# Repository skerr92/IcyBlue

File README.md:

# IcyBlue Feather FPGA Development Board

<image src="https://github.com/skerr92/IcyBlue/blob/main/Images/IMG_0353.jpg">

Welcome to the home of the IcyBlue Feather, an FPGA based development board designed to be integrated into the Adafruit Feather ecosystem of Feathers and Feather Wings.

The goal of this repository is to be the single source of truth for the IcyBlue Feather. Containing all the relevant articles including images, schematics, usage examples, board files, and other important documentation.

Questions? Email [hello@oakdev.tech](mailto:hello@oakdev.tech)

### Documentation ###

All documentation can be found under the [Documentation](https://github.com/skerr92/IcyBlue/tree/main/Documentation) directory of this repository. This will include data sheets, usage guides, application notes, errata, and other important documents.

Documentation quick links:
* Data sheet: [IcyBlue Overview Data Sheet](https://github.com/skerr92/IcyBlue/blob/main/Documentation/IcyBlue%20Feather%20Datasheet%20rev1a.pdf)
* Board files: [EagleCAD Board Files](https://github.com/skerr92/IcyBlue/blob/main/Documentation/Lattice%20FPGA%20standard%20feather%20wing.brd)
* Schematic files: [EagleCAD Schematic Files](https://github.com/skerr92/IcyBlue/blob/main/Documentation/Lattice%20FPGA%20standard%20feather%20wing.sch)

### Schematic ###

Represented below is the Rev 1a schematic. This is the current production schematic for the IcyBlue Feather. If major hardware changes are added, additional labeled schematic images can be found here and in the [documentation directory](https://github.com/skerr92/IcyBlue/tree/main/Documentation).

<image src="https://github.com/skerr92/IcyBlue/blob/main/Images/IcyBlue%20Feather%20Schematic.png">

### Usage Examples ###

All usage examples including the RGB sequence example that ships with the board can be found in the [examples repository](https://github.com/skerr92/ice5lp4k_examples).

Examples Quick Links:
* [RGB Blink](https://github.com/skerr92/ice5lp4k_examples/tree/master/leds)
* [DSP Example](https://github.com/skerr92/ice5lp4k_examples/tree/master/dsp)

### Errata ###

Any Errate for the IcyBlue Feather will be linked below with the specific dates and errata version.

### Additional Information ###

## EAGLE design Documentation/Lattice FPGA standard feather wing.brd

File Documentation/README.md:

# Directory containing relevant documentation

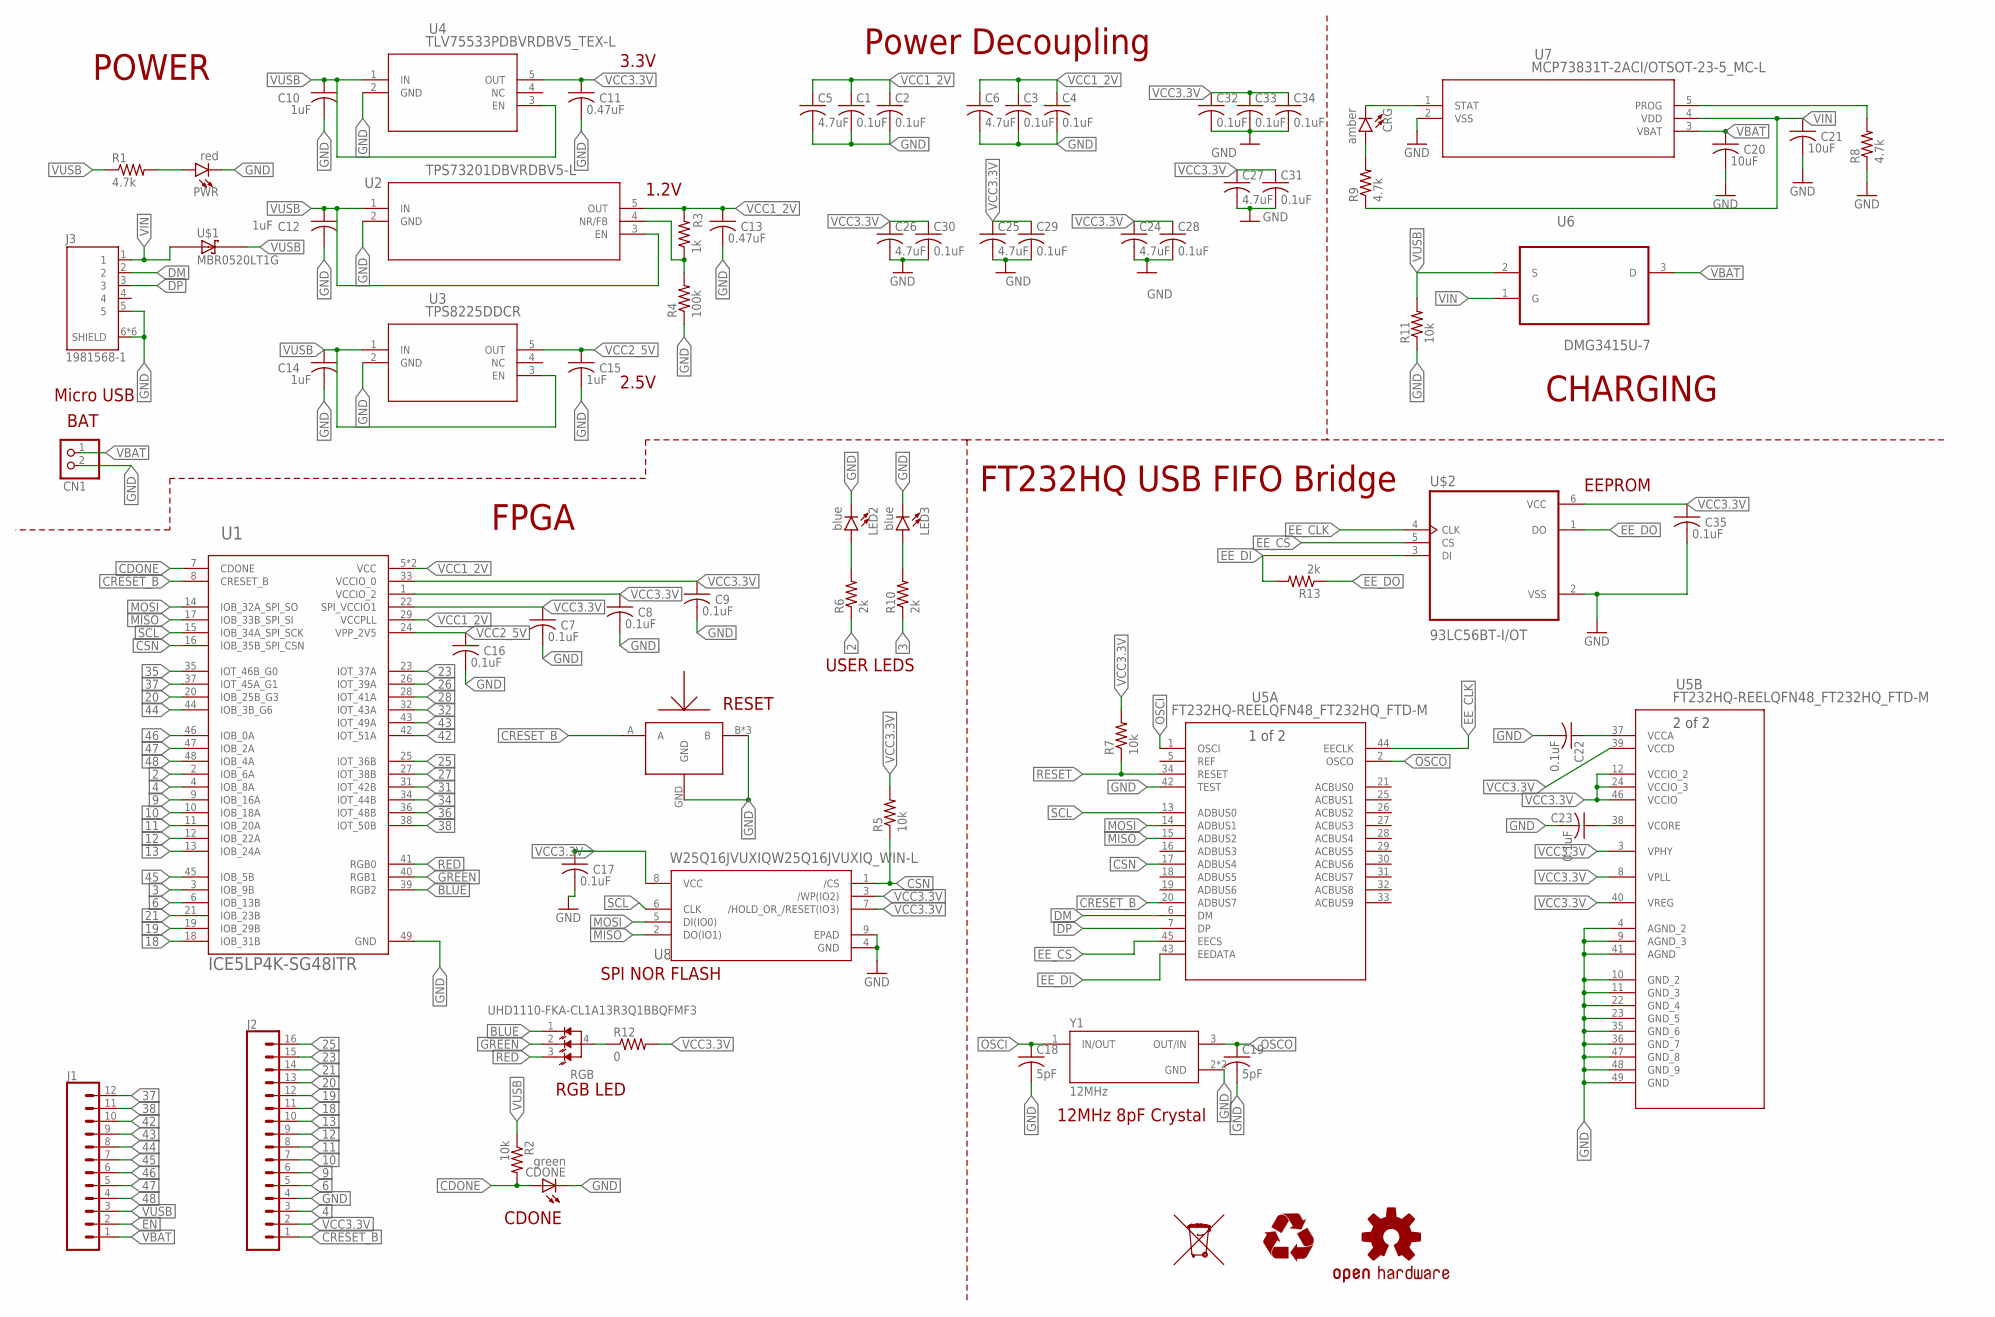
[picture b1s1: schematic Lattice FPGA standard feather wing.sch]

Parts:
C1, C2, C3, C4, C7, C8, C9, C16, C17, C22, C23, C28, C29, C30, C31, C32, C33, C34, C35: 0.1uF; C0402
C5, C6, C24, C25, C26, C27: 4.7uF; C0603
C10, C12, C14, C15: 1uF; C0402
C11, C13: 0.47uF; C0402
C18, C19: 5pF; C0402
C20, C21: 10uF; C0603
CDONE: green; CHIP-LED0603
CN1: JST_2PIN-SMT-RA; JST-PH-2-SMT-RA
CRG: amber; LED-0603
J1: CONN_12NO_SILK; 1X12_NO_SILK
J2: CONN_161X16_NO_SILK; 1X16_NO_SILK
J3: 1981568-1; TE_1981568-1
LED2, LED3: blue; LED-0603
LOGO1: OSHW-LOGOS; OSHW-LOGO-S
PWR: red; LED-0603
R1, R8, R9: 4.7k; R0603
R2, R5, R11: 10k; R0402
R3: 1k; R0402
R4: 100k; R0402
R6, R10, R13: 2k; R0402
R7: 10k; R0603
R12: 0; R0603
RGB: UHD1110-FKA-CL1A13R3Q1BBQFMF3; LED_UHD1110-FKA-CL1A13R3Q1BBQFMF3
U1: ICE5LP4K-SG48ITR; QFN50P700X700X100-49N
U2: TPS73201DBVRDBV5-L; DBV5-L
U3: TPS8225DDCR; DBV5_TEX-L
U4: TLV75533PDBVRDBV5_TEX-L; DBV5_TEX-L
U5: FT232HQ-REELQFN48_FT232HQ_FTD-M; QFN48_FT232HQ_FTD-M
U6: DMG3415U-7; SOT95P240X105-3N
U7: MCP73831T-2ACI/OTSOT-23-5_MC-L; SOT-23-5_MC-L
U8: W25Q16JVUXIQW25Q16JVUXIQ_WIN-L; W25Q16JVUXIQ_WIN-L
U$1: MBR0520LT1G; SOD3716X117(SOD-123)
U$2: 93LC56BT-I/OT; SOT95P280X145-6N
U$3: SOF-232HST; 3.3X2.9
Y1: 12MHz; XTAL_ECS-480-10-37-JTN-TR

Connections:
2: R6.1, U1.2 (IOB_6A)
3: R10.1, U1.3 (IOB_9B)
4: J2.3, U1.4 (IOB_8A)
6: J2.5, U1.6 (IOB_13B)
9: J2.6, U1.9 (IOB_16A)
10: J2.7, U1.10 (IOB_18A)
11: J2.8, U1.11 (IOB_20A)
12: J2.9, U1.12 (IOB_22A)
13: J2.10, U1.13 (IOB_24A)
18: J2.11, U1.18 (IOB_31B)
19: J2.12, U1.19 (IOB_29B)
20: J2.13, U1.20 (IOB_25B_G3)
21: J2.14, U1.21 (IOB_23B)
23: J2.15, U1.23 (IOT_37A)
25: J2.16, U1.25 (IOT_36B)
26: U1.26 (IOT_39A)
27: U1.27 (IOT_38B)
28: U1.28 (IOT_41A)
31: U1.31 (IOT_42B)
32: U1.32 (IOT_43A)
34: U1.34 (IOT_44B)
35: U1.35 (IOT_46B_G0)
36: U1.36 (IOT_48B)
37: J1.12, U1.37 (IOT_45A_G1)
38: J1.11, U1.38 (IOT_50B)
42: J1.10, U1.42 (IOT_51A)
43: J1.9, U1.43 (IOT_49A)
44: J1.8, U1.44 (IOB_3B_G6)
45: J1.7, U1.45 (IOB_5B)
46: J1.6, U1.46 (IOB_0A)
47: J1.5, U1.47 (IOB_2A)
48: J1.4, U1.48 (IOB_4A)
BLUE: RGB.1 (BLUE), U1.39 (RGB2)
CDONE: CDONE.A, R2.2, U1.7 (CDONE)
CRESET_B: J2.1, U1.8 (CRESET_B), U5.20 (ADBUS7), U$3.A
CSN: R5.1, U1.16 (IOB_35B_SPI_CSN), U5.17 (ADBUS4), U8.1 (/CS)
DM: J3.2, U5.6 (DM)
DP: J3.3, U5.7 (DP)
EE_CLK: U5.44 (EECLK), U$2.4 (CLK)
EE_CS: U5.45 (EECS), U$2.5 (CS)
EE_DI: R13.2, U5.43 (EEDATA), U$2.3 (DI)
EE_DO: R13.1, U$2.1 (DO)
EN: J1.2
GND: C1.2, C2.2, C3.2, C4.2, C5.2, C6.2, C7.2, C8.2, C9.2, C10.2, C11.2, C12.2, C13.2, C14.2, C15.2, C16.2, C17.2, C18.2, C19.2, C20.2, C21.2, C22.2, C23.2, C24.2, C25.2, C26.2, C27.2, C28.2, C29.2, C30.2, C31.2, C32.2, C33.2, C34.2, C35.2, CDONE.C, CN1.2 (1), J2.4, J3.5, J3.6 (SHIELD), J3.7 (SHIELD), J3.8 (SHIELD), J3.9 (SHIELD), J3.10 (SHIELD), J3.11 (SHIELD), LED2.C, LED3.C, PWR.C, R4.1, R8.1, R11.1, U1.49 (GND), U2.2 (GND), U3.2 (GND), U4.2 (GND), U5.4 (AGND_2), U5.9 (AGND_3), U5.10 (GND_2), U5.11 (GND_3), U5.22 (GND_4), U5.23 (GND_5), U5.35 (GND_6), U5.36 (GND_7), U5.41 (AGND), U5.42 (TEST), U5.47 (GND_8), U5.48 (GND_9), U5.49 (GND), U7.2 (VSS), U8.4 (GND), U8.9 (EPAD), U$2.2 (VSS), U$3.B, U$3.B2 (B), U$3.B3 (B), U$3.GND, Y1.2 (GND), Y1.4 (GND)
GREEN: RGB.2 (GREEN), U1.40 (RGB1)
MISO: U1.17 (IOB_33B_SPI_SI), U5.15 (ADBUS2), U8.2 (DO(IO1))
MOSI: U1.14 (IOB_32A_SPI_SO), U5.14 (ADBUS1), U8.5 (DI(IO0))
unnamed: R3.1, R4.2, U2.4 (NR/FB)
unnamed: R8.2, U7.5 (PROG)
unnamed: C23.1, U5.38 (VCORE)
unnamed: CRG.C, U7.1 (STAT)
unnamed: CRG.A, R9.2
unnamed: R12.1, RGB.4 (ANODE)
unnamed: PWR.A, R1.2
unnamed: C22.1, U5.37 (VCCA)
unnamed: LED2.A, R6.2
unnamed: LED3.A, R10.2
OSCI: C18.1, U5.1 (OSCI), Y1.1 (IN/OUT)
OSCO: C19.1, U5.2 (OSCO), Y1.3 (OUT/IN)
RED: RGB.3 (RED), U1.41 (RGB0)
RESET: R7.1, U5.34 (RESET)
SCL: U1.15 (IOB_34A_SPI_SCK), U5.13 (ADBUS0), U8.6 (CLK)
VBAT: C20.1, CN1.1 (2), J1.1, U6.3 (D), U7.3 (VBAT)
VCC1_2V: C1.1, C2.1, C3.1, C4.1, C5.1, C6.1, C13.1, R3.2, U1.5 (VCC), U1.29 (VCCPLL), U1.30 (VCC), U2.5 (OUT)
VCC2_5V: C15.1, C16.1, U1.24 (VPP_2V5), U3.5 (OUT)
VCC3.3V: C7.1, C8.1, C9.1, C11.1, C17.1, C24.1, C25.1, C26.1, C27.1, C28.1, C29.1, C30.1, C31.1, C32.1, C33.1, C34.1, C35.1, J2.2, R5.2, R7.2, R12.2, U1.1 (VCCIO_2), U1.22 (SPI_VCCIO1), U1.33 (VCCIO_0), U4.5 (OUT), U5.3 (VPHY), U5.8 (VPLL), U5.12 (VCCIO_2), U5.24 (VCCIO_3), U5.39 (VCCD), U5.40 (VREG), U5.46 (VCCIO), U8.3 (/WP(IO2)), U8.7 (/HOLD_OR_/RESET(IO3)), U8.8 (VCC), U$2.6 (VCC)
VIN: C21.1, J3.1, R9.1, U6.1 (G), U7.4 (VDD), U$1.2 (A)
VUSB: C10.1, C12.1, C14.1, J1.3, R1.1, R2.1, R11.2, U2.1 (IN), U2.3 (EN), U3.1 (IN), U3.3 (EN), U4.1 (IN), U4.3 (EN), U6.2 (S), U$1.1 (C)

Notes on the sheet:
SPI NOR FLASH
FPGA
POWER
BAT
CHARGING
EEPROM
FT232HQ USB FIFO Bridge
12MHz 8pF Crystal
RGB LED
CDONE
RESET
USER LEDS
1.2V
2.5V
3.3V
Power Decoupling
Micro USB

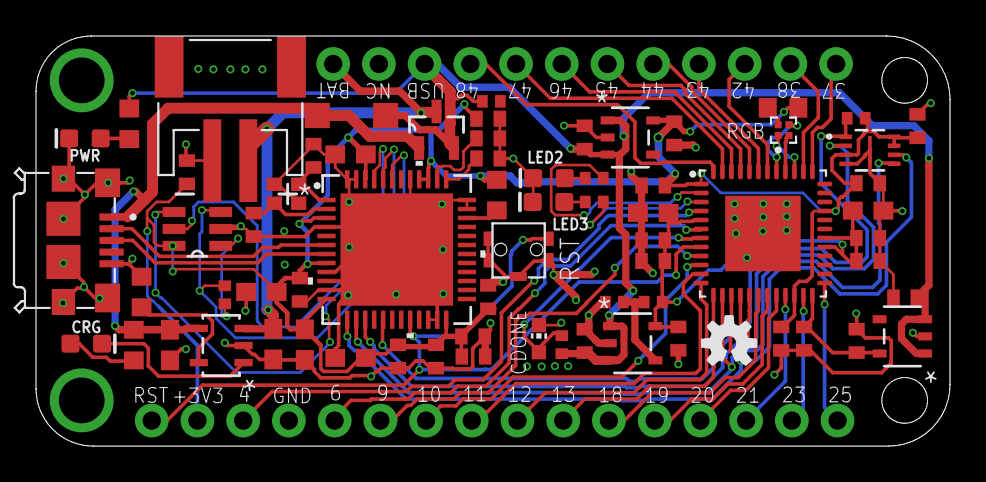
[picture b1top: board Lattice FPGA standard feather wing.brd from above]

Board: 2 copper layers, 50.8 x 22.8 mm, 71 parts (0 on the bottom side), 59 nets.

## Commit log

2023-02-19 Add files via upload
    product photo
2023-02-19 add main product image
2023-02-19 adding eagle cad files
2023-02-19 Fix typo

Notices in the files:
parts and their libraries:
SparkFun-Connectors: Licensing: Creative Commons ShareAlike 4.0 International - https://creativecommons.org/licenses/by-sa/4.0
COPYRIGHT: Copyright (C) 2018 Accelerated Designs. All rights reserved
